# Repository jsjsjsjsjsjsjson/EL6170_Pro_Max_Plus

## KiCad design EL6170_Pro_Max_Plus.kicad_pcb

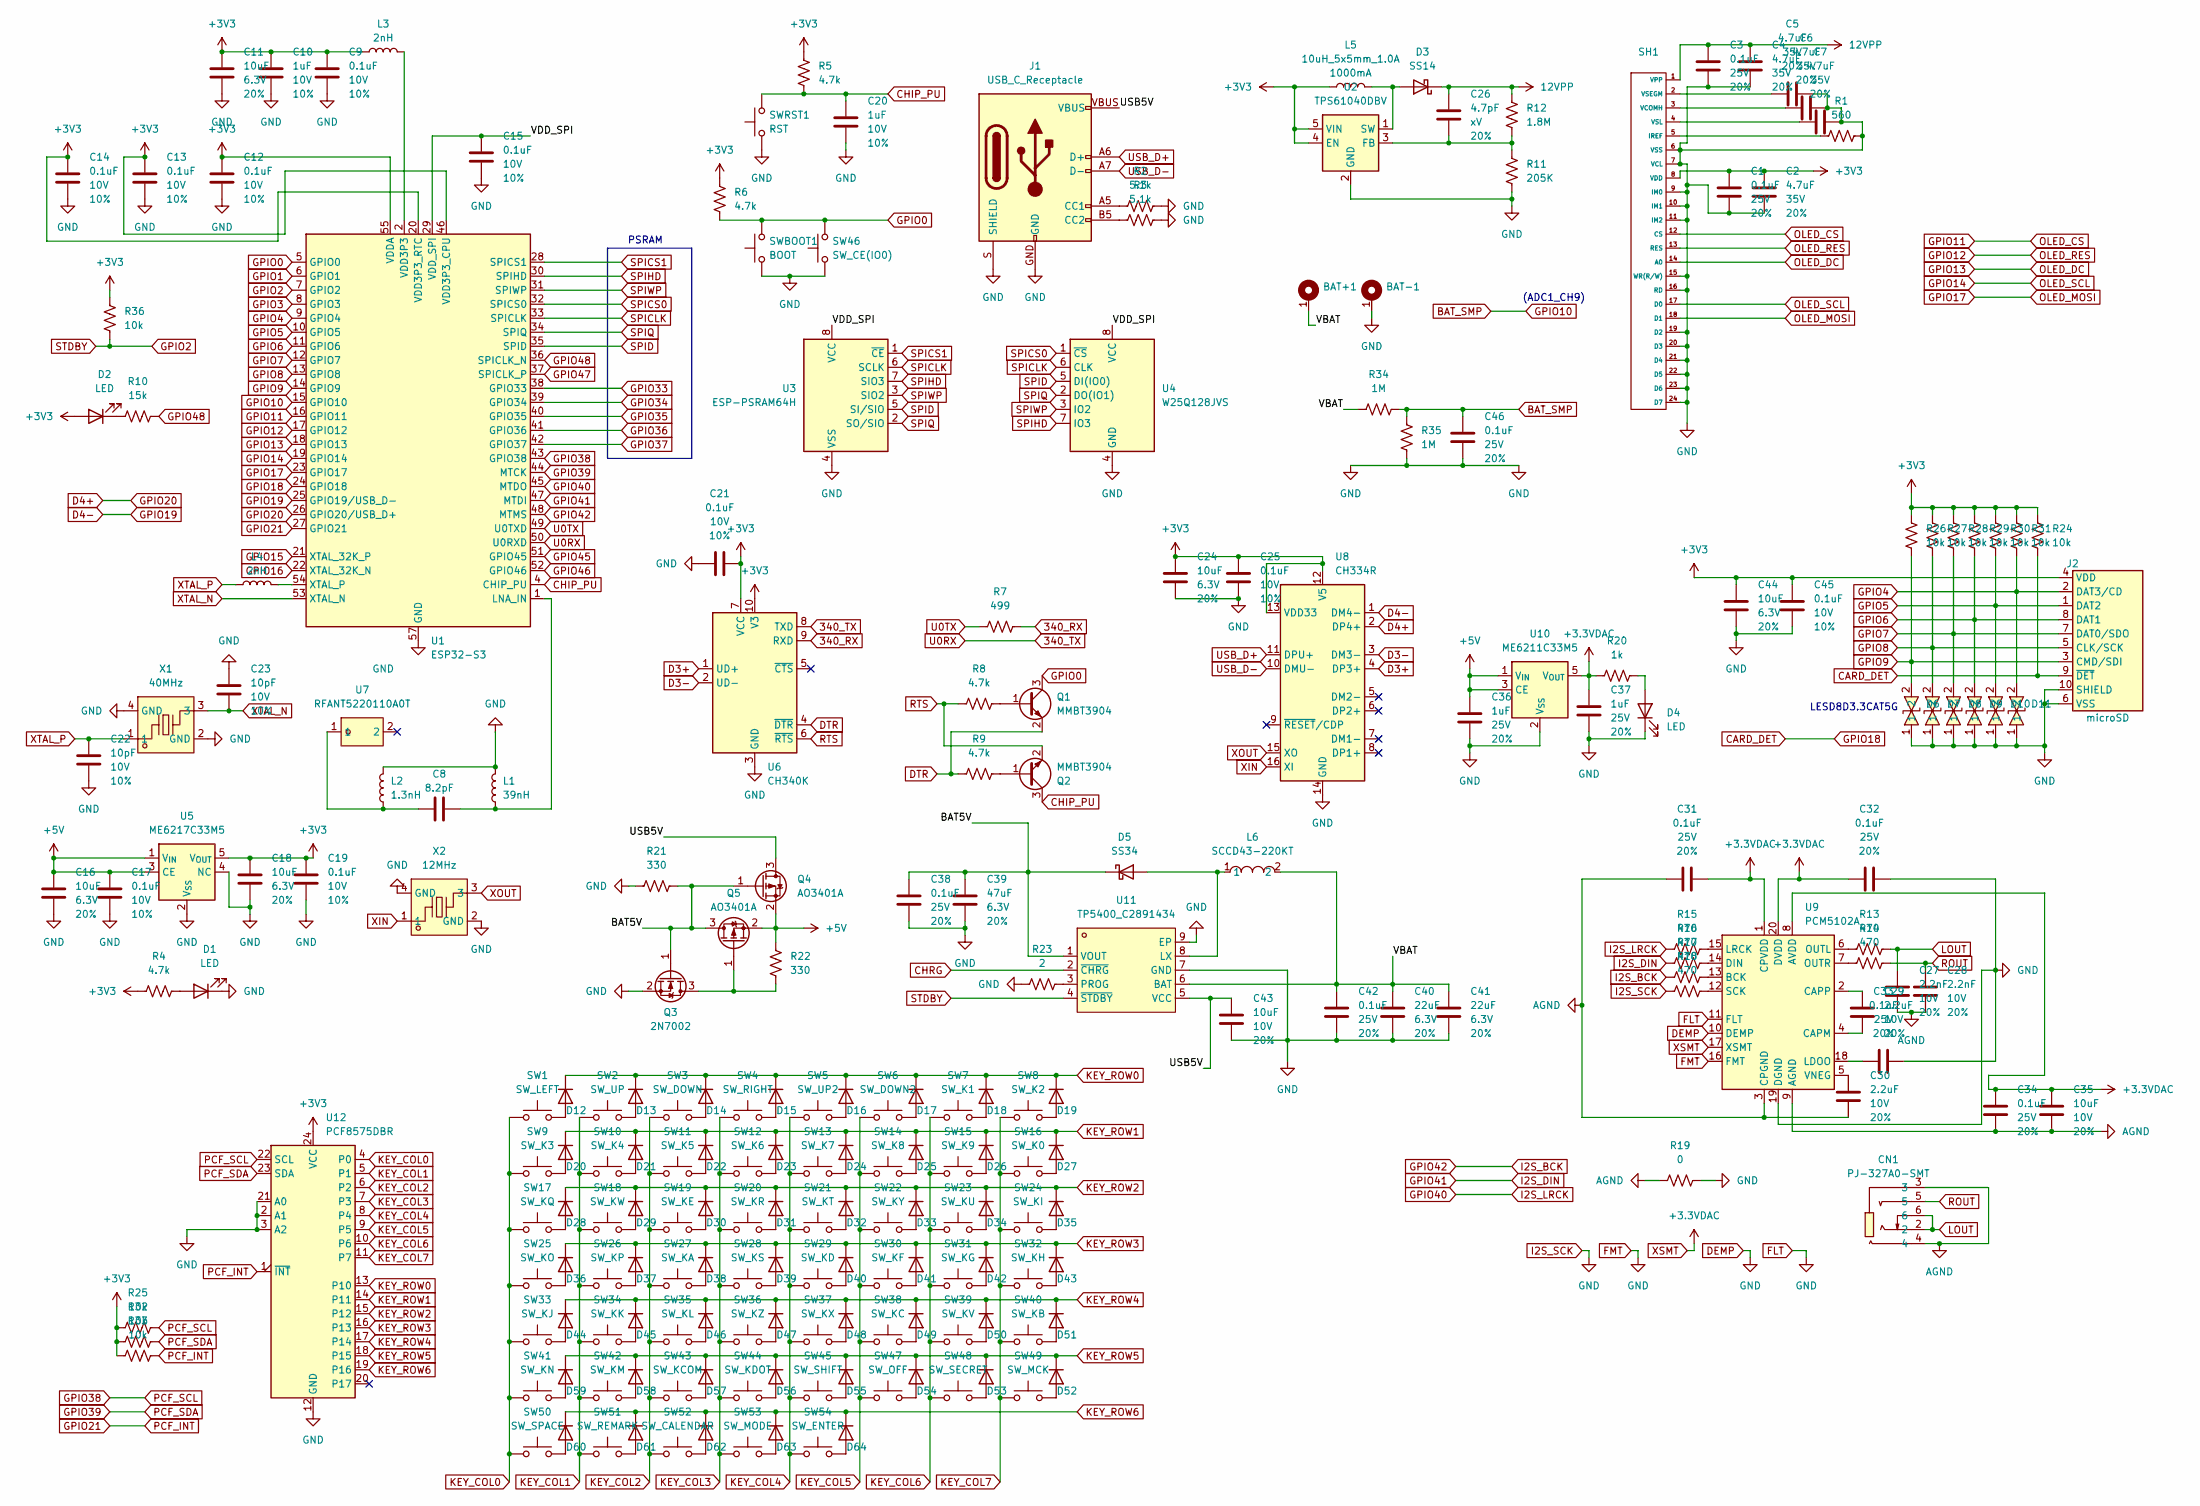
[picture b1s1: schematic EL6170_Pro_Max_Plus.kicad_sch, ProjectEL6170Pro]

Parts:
BAT+1: TestPoint_Pad_2.0x2.0mm
BAT-1: TestPoint_Pad_2.0x2.0mm
C1, C3, C31, C32, C33, C34, C38, C42, C46: 0.1uF; C_0603_1608Metric; Voltage 25V; Tolerance 20%
C2, C4, C5, C6, C7: 4.7uF; C_0603_1608Metric; Voltage 35V; Tolerance 20%
C8: 8.2pF; C_0402_1005Metric
C9, C12, C13, C14, C15, C17, C19, C21, C25, C45: 0.1uF; C_0402_1005Metric; Voltage 10V; Tolerance 10%
C10, C20: 1uF; C_0402_1005Metric; Voltage 10V; Tolerance 10%
C11, C16, C18, C24, C44: 10uF; C_0402_1005Metric; Voltage 6.3V; Tolerance 20%
C22, C23: 10pF; C_0603_1608Metric; Voltage 10V; Tolerance 10%
C26: 4.7pF; C_0402_1005Metric; Voltage xV; Tolerance 20%
C27, C28: 2.2nF; C_0603_1608Metric; Voltage 10V; Tolerance 20%
C29, C30: 2.2uF; C_0603_1608Metric; Voltage 10V; Tolerance 20%
C35, C43: 10uF; C_0603_1608Metric; Voltage 10V; Tolerance 20%
C36, C37: 1uF; C_0603_1608Metric; Voltage 25V; Tolerance 20%
C39: 47uF; C_0805_2012Metric; Voltage 6.3V; Tolerance 20%
C40, C41: 22uF; C_0603_1608Metric; Voltage 6.3V; Tolerance 20%
CN1: PJ-327A0-SMT; AUDIO-SMD_PJ-327A0-SMT; LCSC Part C381135
D1, D2, D4: LED; LED_0603_1608Metric
D3: SS14; D_SMA
D5: SS34; D_SMA
D6, D7, D8, D9, D10, D11: LESD8D3.3CAT5G; D_SOD-882; LCSC Part C172409
D12, D13, D14, D15, D16, D17, D18, D19, D20, D21, D22, D23, D24, D25, D26, D27, D28, D29, D30, D31, D32, D33, D34, D35, D36, D37, D38, D39, D40, D41, D42, D43, D44, D45, D46, D47, D48, D49, D50, D51, D52, D53, D54, D55, D56, D57, D58, D59, D60, D61, D62, D63, D64: 1N4148WS; D_SOD-323
J1: USB_C_Receptacle; USB-C_16
J2: microSD; microSD_External_Pin
L1: 39nH; L_0402_1005Metric
L2: 1.3nH; L_0402_1005Metric
L3, L4: 2nH; L_0402_1005Metric
L5: 10uH_5x5mm_1.0A; Inductor_4.7x4.7mm
L6: SCCD43-220KT; IND-SMD_L4.5-W4.0_SCCD43; LCSC Part C532863
Q1, Q2: MMBT3904; SOT-23
Q3: 2N7002; SOT-23
Q4, Q5: AO3401A; SOT-23
R1: 560; R_0402_1005Metric
R2, R3: 5.1k; R_0402_1005Metric
R4, R5, R6, R8, R9: 4.7k; R_0402_1005Metric
R7: 499; R_0402_1005Metric
R10: 15k; R_0603_1608Metric
R11: 205K; R_0603_1608Metric
R12: 1.8M; R_0603_1608Metric
R13, R14, R15, R16, R17, R18: 470; R_0603_1608Metric
R19: 0; R_0603_1608Metric
R20: 1k; R_0603_1608Metric
R21, R22: 330; R_0603_1608Metric
R23: 2; R_0603_1608Metric
R24, R25, R26, R27, R28, R29, R30, R31, R32, R33, R36: 10k; R_0402_1005Metric
R34, R35: 1M; R_0603_1608Metric
SH1: SH1122_FPC
SW1: SW_LEFT; MaskBtm6mmBh
SW2: SW_UP; MaskBtm6mm
SW3: SW_DOWN; MaskBtm6mm
SW4: SW_RIGHT; MaskBtm6mmBh
SW5: SW_UP2; MaskBtm6mm
SW6: SW_DOWN2; MaskBtm6mm
SW7: SW_K1; MaskBtm4mmBh
SW8: SW_K2; MaskBtm4mmBh
SW9: SW_K3; MaskBtm4mmBh
SW10: SW_K4; MaskBtm4mmBh
SW11: SW_K5; MaskBtm4mmBh
SW12: SW_K6; MaskBtm4mmBh
SW13: SW_K7; MaskBtm4mmBh
SW14: SW_K8; MaskBtm4mmBh
SW15: SW_K9; MaskBtm4mmBh
SW16: SW_K0; MaskBtm4mmBh
SW17: SW_KQ; MaskBtm5mm
SW18: SW_KW; MaskBtm5mm
SW19: SW_KE; MaskBtm5mm
SW20: SW_KR; MaskBtm5mm
SW21: SW_KT; MaskBtm5mm
SW22: SW_KY; MaskBtm5mm
SW23: SW_KU; MaskBtm5mm
SW24: SW_KI; MaskBtm5mm
SW25: SW_KO; MaskBtm5mm
SW26: SW_KP; MaskBtm5mm
SW27: SW_KA; MaskBtm5mm
SW28: SW_KS; MaskBtm5mm
SW29: SW_KD; MaskBtm5mm
SW30: SW_KF; MaskBtm5mm
SW31: SW_KG; MaskBtm5mm
SW32: SW_KH; MaskBtm5mm
SW33: SW_KJ; MaskBtm5mm
SW34: SW_KK; MaskBtm5mm
SW35: SW_KL; MaskBtm5mm
SW36: SW_KZ; MaskBtm5mm
SW37: SW_KX; MaskBtm5mm
SW38: SW_KC; MaskBtm5mm
SW39: SW_KV; MaskBtm5mm
SW40: SW_KB; MaskBtm5mm
SW41: SW_KN; MaskBtm5mm
SW42: SW_KM; MaskBtm5mm
SW43: SW_KCOM; MaskBtm5mm
SW44: SW_KDOT; MaskBtm5mm
SW45: SW_SHIFT; MaskBtm5mm
SW46: SW_CE(IO0); MaskBtm5mm
SW47: SW_OFF; MaskBtm5mm
SW48: SW_SECRET; MaskBtm5mm
SW49: SW_MCK; MaskBtm5mm
SW50: SW_SPACE; MaskBtm5mmBh
SW51: SW_REMARK; MaskBtm5mm
SW52: SW_CALENDAR; MaskBtm5mm
SW53: SW_MODE; MaskBtm5mm
SW54: SW_ENTER; MaskBtm5mmBh
SWBOOT1: BOOT; MaskBtm4mm
SWRST1: RST; MaskBtm4mm
U1: ESP32-S3; QFN-56-1EP_7x7mm_P0.4mm_EP4x4mm
U2: TPS61040DBV; SOT-23-5
U3: ESP-PSRAM64H; SOIC-8_3.9x4.9mm_P1.27mm
U4: W25Q128JVS; SOIC-8_5.23x5.23mm_P1.27mm
U5: ME6217C33M5; SOT-23-5
U6: CH340K; SSOP-10-1EP_3.9x4.9mm_P1mm_EP2.1x3.3mm
U7: RFANT5220110A0T; FILTER-SMD_L5.2-W2.0-L; LCSC Part C127611
U8: CH334R; QSOP-16_3.9x4.9mm_P0.635mm
U9: PCM5102A; TSSOP-20_4.4x6.5mm_P0.65mm
U10: ME6211C33M5; SOT-23-5
U11: TP5400_C2891434; ESOP-8_L4.9-W3.9-P1.27-LS6.0-BL-EP; LCSC Part C2891434
U12: PCF8575DBR; SSOP-24_5.3x8.2mm_P0.65mm
X1: 40MHz; CRYSTAL-SMD_4P-L2.5-W2.0-BL; LCSC Part C555614
X2: 12MHz; CRYSTAL-SMD_4P-L2.5-W2.0-BL-A; LCSC Part C2896601

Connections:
12VPP: C3.1, C4.1, C26.2, D3.1 (K), R12.1, SH1.1 (VPP)
340_RX: R7.1, U6.9 (RXD)
340_TX: U1.50 (U0RXD), U6.8 (TXD)
+3V3: C1.1, C2.1, C9.1, C10.1, C11.1, C12.1, C13.1, C14.1, C18.1, C19.1, C21.2, C24.1, C25.1, C44.1, C45.1, D2.2 (A), J2.4 (VDD), L3.1, L5.1, R4.2, R5.1, R6.1, R24.1, R25.1, R26.1, R27.1, R28.1, R29.1, R30.1, R31.1, R32.1, R33.1, R36.1, SH1.8 (VDD), U1.20 (VDD3P3_RTC), U1.46 (VDD3P3_CPU), U1.55 (VDDA), U1.56 (VDDA), U2.4 (EN), U2.5 (VIN), U5.5 (V_{OUT}), U6.7 (VCC), U6.10 (V3), U8.12 (V5), U8.13 (VDD33), U12.24 (VCC)
+5V: C16.1, C17.1, C36.1, Q4.2 (S), Q5.2 (S), R22.1, U5.1 (V_{IN}), U5.3 (CE), U10.1 (V_{IN}), U10.3 (CE)
/BAT5V: C38.1, C39.1, D5.1 (K), Q3.1 (G), Q4.1 (G), Q5.3 (D), R21.1, U11.1 (VOUT)
/USB5V: C43.1, J1.VBUS, Q4.3 (D), U11.5 (VCC)
/VBAT: BAT+1.1, C40.1, C41.1, C42.1, L6.2, R34.2, U11.6 (BAT)
/VDD_SPI: C15.1, U1.29 (VDD_SPI), U3.8 (VCC), U4.8 (VCC)
AGND: C27.2, C28.2, C30.2, C31.1, C34.1, C35.2, CN1.3, CN1.4, R19.2, U9.3 (CPGND), U9.9 (AGND)
BAT_SMP: C46.1, R34.1, R35.1, U1.15 (GPIO10)
CARD_DET: J2.9 (~DET), R24.2, U1.24 (GPIO18)
CHIP_PU: C20.1, Q2.3 (C), R5.2, SWRST1.2, U1.4 (CHIP_PU)
CHRG: U11.2 (~CHRG)
D3+: U6.1 (UD+), U8.4 (DP3+)
D3-: U6.2 (UD-), U8.3 (DM3-)
D4+: U1.26 (GPIO20/USB_D+), U8.2 (DP4+)
D4-: U1.25 (GPIO19/USB_D-), U8.1 (DM4-)
DEMP: BAT-1.1, C1.2, C2.2, C3.2, C4.2, C5.2, C6.2, C7.2, C9.2, C10.2, C11.2, C12.2, C13.2, C14.2, C15.2, C16.2, C17.2, C18.2, C19.2, C20.2, C21.1, C22.2, C23.1, C24.2, C25.2, C32.2, C33.2, C36.2, C37.2, C38.2, C39.2, C40.2, C41.2, C42.2, C43.2, C44.2, C45.2, C46.2, D1.1 (K), D4.1 (K), D6.1, D7.1, D8.1, D9.1, D10.1, D11.1, J1.GND, J1.S (SHIELD), J2.6 (VSS), J2.10 (SHIELD), L1.2, L2.2, Q3.2 (S), R1.1, R2.1, R3.1, R11.2, R18.2, R19.1, R21.2, R23.2, R35.2, SH1.6 (VSS), SH1.7 (VCL), SH1.9 (IM0), SH1.10 (IM1), SH1.11 (IM2), SH1.15 (WR(R/W)), SH1.16 (RD), SH1.19 (D2), SH1.20 (D3), SH1.21 (D4), SH1.22 (D5), SH1.23 (D6), SH1.24 (D7), SW46.1, SWBOOT1.1, SWRST1.1, U1.57 (GND), U2.2 (GND), U3.4 (VSS), U4.4 (GND), U5.2 (V_{SS}), U5.4 (NC), U6.3 (GND), U6.11 (GND), U8.14 (GND), U9.10 (DEMP), U9.11 (FLT), U9.16 (FMT), U9.19 (DGND), U10.2 (V_{SS}), U11.7 (GND), U11.9 (EP), U12.2 (A1), U12.3 (A2), U12.12 (GND), U12.21 (A0), X1.2 (GND), X1.4 (GND), X2.2 (GND), X2.4 (GND)
DTR: Q1.2 (E), R9.1, U6.4 (~DTR)
GPIO0: Q1.3 (C), R6.2, SW46.2, SWBOOT1.2, U1.5 (GPIO0)
GPIO1: U1.6 (GPIO1)
GPIO2: R36.2, U1.7 (GPIO2), U11.4 (~STDBY)
GPIO3: U1.8 (GPIO3)
GPIO4: D11.2, J2.2 (DAT3/CD), R31.2, U1.9 (GPIO4)
GPIO5: D10.2, J2.1 (DAT2), R30.2, U1.10 (GPIO5)
GPIO6: D9.2, J2.8 (DAT1), R29.2, U1.11 (GPIO6)
GPIO7: D8.2, J2.7 (DAT0/SDO), R28.2, U1.12 (GPIO7)
GPIO8: D7.2, J2.5 (CLK/SCK), R27.2, U1.13 (GPIO8)
GPIO9: D6.2, J2.3 (CMD/SDI), R26.2, U1.14 (GPIO9)
GPIO11: SH1.12 (CS), U1.16 (GPIO11)
GPIO12: SH1.13 (RES), U1.17 (GPIO12)
GPIO13: SH1.14 (A0), U1.18 (GPIO13)
GPIO14: SH1.17 (D0), U1.19 (GPIO14)
GPIO15: U1.21 (XTAL_32K_P)
GPIO16: U1.22 (XTAL_32K_N)
GPIO17: SH1.18 (D1), U1.23 (GPIO17)
GPIO21: R33.2, U1.27 (GPIO21), U12.1 (~INT)
GPIO33: U1.38 (GPIO33)
GPIO34: U1.39 (GPIO34)
GPIO35: U1.40 (GPIO35)
GPIO36: U1.41 (GPIO36)
GPIO37: U1.42 (GPIO37)
GPIO38: R25.2, U1.43 (GPIO38), U12.22 (SCL)
GPIO39: R32.2, U1.44 (MTCK), U12.23 (SDA)
GPIO40: R15.2, U1.45 (MTDO)
GPIO41: R16.2, U1.47 (MTDI)
GPIO42: R17.2, U1.48 (MTMS)
GPIO45: U1.51 (GPIO45)
GPIO46: U1.52 (GPIO46)
GPIO47: U1.37 (SPICLK_P)
GPIO48: R10.1, U1.36 (SPICLK_N)
KEY_COL0: SW1.1, SW9.1, SW17.1, SW25.1, SW33.1, SW41.1, SW50.1, U12.4 (P0)
KEY_COL1: SW2.1, SW10.1, SW18.1, SW26.1, SW34.1, SW42.1, SW51.1, U12.5 (P1)
KEY_COL2: SW3.1, SW11.1, SW19.1, SW27.1, SW35.1, SW43.1, SW52.1, U12.6 (P2)
KEY_COL3: SW4.1, SW12.1, SW20.1, SW28.1, SW36.1, SW44.1, SW53.1, U12.7 (P3)
KEY_COL4: SW5.1, SW13.1, SW21.1, SW29.1, SW37.1, SW45.1, SW54.1, U12.8 (P4)
KEY_COL5: SW6.1, SW14.1, SW22.1, SW30.1, SW38.1, SW47.1, U12.9 (P5)
KEY_COL6: SW7.1, SW15.1, SW23.1, SW31.1, SW39.1, SW48.1, U12.10 (P6)
KEY_COL7: SW8.1, SW16.1, SW24.1, SW32.1, SW40.1, SW49.1, U12.11 (P7)
KEY_ROW0: D12.1 (K), D13.1 (K), D14.1 (K), D15.1 (K), D16.1 (K), D17.1 (K), D18.1 (K), D19.1 (K), U12.13 (P10)
KEY_ROW1: D20.1 (K), D21.1 (K), D22.1 (K), D23.1 (K), D24.1 (K), D25.1 (K), D26.1 (K), D27.1 (K), U12.14 (P11)
KEY_ROW2: D28.1 (K), D29.1 (K), D30.1 (K), D31.1 (K), D32.1 (K), D33.1 (K), D34.1 (K), D35.1 (K), U12.15 (P12)
KEY_ROW3: D36.1 (K), D37.1 (K), D38.1 (K), D39.1 (K), D40.1 (K), D41.1 (K), D42.1 (K), D43.1 (K), U12.16 (P13)
KEY_ROW4: D44.1 (K), D45.1 (K), D46.1 (K), D47.1 (K), D48.1 (K), D49.1 (K), D50.1 (K), D51.1 (K), U12.17 (P14)
KEY_ROW5: D52.1 (K), D53.1 (K), D54.1 (K), D55.1 (K), D56.1 (K), D57.1 (K), D58.1 (K), D59.1 (K), U12.18 (P15)
KEY_ROW6: D60.1 (K), D61.1 (K), D62.1 (K), D63.1 (K), D64.1 (K), U12.19 (P16)
LOUT: C27.1, CN1.2, CN1.6, R13.1
unnamed: C8.2, L2.1, U7.1
unnamed: D1.2 (A), R4.1
unnamed: D2.1 (K), R10.2
unnamed: D3.2 (A), L5.2, U2.1 (SW)
unnamed: D4.2 (A), R20.1
unnamed: D5.2 (A), L6.1, U11.8 (LX)
unnamed: D12.2 (A), SW1.2
unnamed: D13.2 (A), SW2.2
unnamed: D14.2 (A), SW3.2
unnamed: D15.2 (A), SW4.2
unnamed: D16.2 (A), SW5.2
unnamed: D17.2 (A), SW6.2
unnamed: D18.2 (A), SW7.2
unnamed: D19.2 (A), SW8.2
unnamed: D20.2 (A), SW9.2
unnamed: D21.2 (A), SW10.2
unnamed: D22.2 (A), SW11.2
unnamed: D23.2 (A), SW12.2
unnamed: D24.2 (A), SW13.2
unnamed: D25.2 (A), SW14.2
unnamed: D26.2 (A), SW15.2
unnamed: D27.2 (A), SW16.2
unnamed: D28.2 (A), SW17.2
unnamed: D29.2 (A), SW18.2
unnamed: D30.2 (A), SW19.2
unnamed: D31.2 (A), SW20.2
unnamed: D32.2 (A), SW21.2
unnamed: D33.2 (A), SW22.2
unnamed: D34.2 (A), SW23.2
unnamed: D35.2 (A), SW24.2
unnamed: D36.2 (A), SW25.2
unnamed: D37.2 (A), SW26.2
unnamed: D38.2 (A), SW27.2
unnamed: D39.2 (A), SW28.2
unnamed: D40.2 (A), SW29.2
unnamed: D41.2 (A), SW30.2
unnamed: D42.2 (A), SW31.2
unnamed: D43.2 (A), SW32.2
unnamed: D44.2 (A), SW33.2
unnamed: D45.2 (A), SW34.2
unnamed: D46.2 (A), SW35.2
unnamed: D47.2 (A), SW36.2
unnamed: D48.2 (A), SW37.2
unnamed: D49.2 (A), SW38.2
unnamed: D50.2 (A), SW39.2
unnamed: D51.2 (A), SW40.2
unnamed: D52.2 (A), SW49.2
unnamed: D53.2 (A), SW48.2
unnamed: D54.2 (A), SW47.2
unnamed: D55.2 (A), SW45.2
unnamed: D56.2 (A), SW44.2
unnamed: D57.2 (A), SW43.2
unnamed: D58.2 (A), SW42.2
unnamed: D59.2 (A), SW41.2
unnamed: D60.2 (A), SW50.2
unnamed: D61.2 (A), SW51.2
unnamed: D62.2 (A), SW52.2
unnamed: D63.2 (A), SW53.2
unnamed: D64.2 (A), SW54.2
unnamed: J1.A5 (CC1), R2.2
unnamed: J1.B5 (CC2), R3.2
unnamed: L3.2, U1.2 (VDD3P3), U1.3 (VDD3P3)
unnamed: Q1.1 (B), R8.2
unnamed: Q2.1 (B), R9.2
unnamed: Q3.3 (D), Q5.1 (G), R22.2
unnamed: R1.2, SH1.5 (IREF)
unnamed: C6.1, SH1.3 (VCOMH)
unnamed: C5.1, SH1.2 (VSEGM)
unnamed: C7.1, SH1.4 (VSL)
unnamed: C8.1, L1.1, U1.1 (LNA_IN)
unnamed: L4.2, U1.54 (XTAL_P)
unnamed: C26.1, R11.1, R12.2, U2.3 (FB)
unnamed: R17.1, U9.13 (BCK)
unnamed: C29.2, U9.4 (CAPM)
unnamed: C29.1, U9.2 (CAPP)
unnamed: R16.1, U9.14 (DIN)
unnamed: C33.1, U9.18 (LDOO)
unnamed: R15.1, U9.15 (LRCK)
unnamed: R13.2, U9.6 (OUTL)
unnamed: R14.2, U9.7 (OUTR)
unnamed: R18.1, U9.12 (SCK)
unnamed: C30.1, U9.5 (VNEG)
unnamed: R23.1, U11.3 (PROG)
ROUT: C28.1, CN1.5, R14.1
RTS: Q2.2 (E), R8.1, U6.6 (~RTS)
SPICLK: U1.33 (SPICLK), U3.6 (SCLK), U4.6 (CLK)
SPICS0: U1.32 (SPICS0), U4.1 (~CS)
SPICS1: U1.28 (SPICS1), U3.1 (~CE)
SPID: U1.35 (SPID), U3.5 (SI/SIO), U4.5 (DI(IO0))
SPIHD: U1.30 (SPIHD), U3.7 (SIO3), U4.7 (IO3)
SPIQ: U1.34 (SPIQ), U3.2 (SO/SIO), U4.2 (DO(IO1))
SPIWP: U1.31 (SPIWP), U3.3 (SIO2), U4.3 (IO2)
U0TX: R7.2, U1.49 (U0TXD)
USB_D+: J1.A6 (D+), J1.B6 (D+), U8.11 (DPU+)
USB_D-: J1.A7 (D-), J1.B7 (D-), U8.10 (DMU-)
XIN: U8.16 (XI), X2.1
XOUT: U8.15 (XO), X2.3
XSMT: C31.2, C32.1, C34.2, C35.1, C37.1, R20.2, U9.1 (CPVDD), U9.8 (AVDD), U9.17 (XSMT), U9.20 (DVDD), U10.5 (V_{OUT})
XTAL_N: C23.2, U1.53 (XTAL_N), X1.3
XTAL_P: C22.1, L4.1, X1.1

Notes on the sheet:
LESD8D3.3CAT5G
(ADC1_CH9)
PSRAM

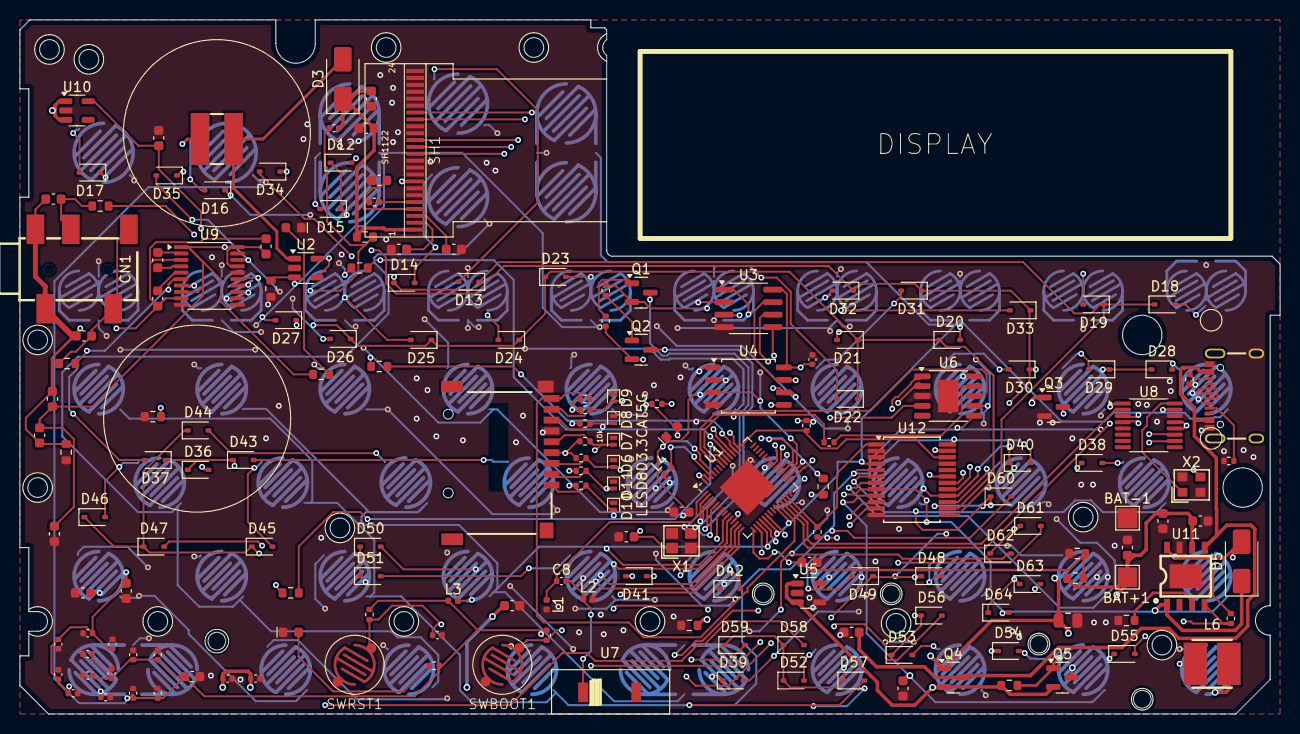
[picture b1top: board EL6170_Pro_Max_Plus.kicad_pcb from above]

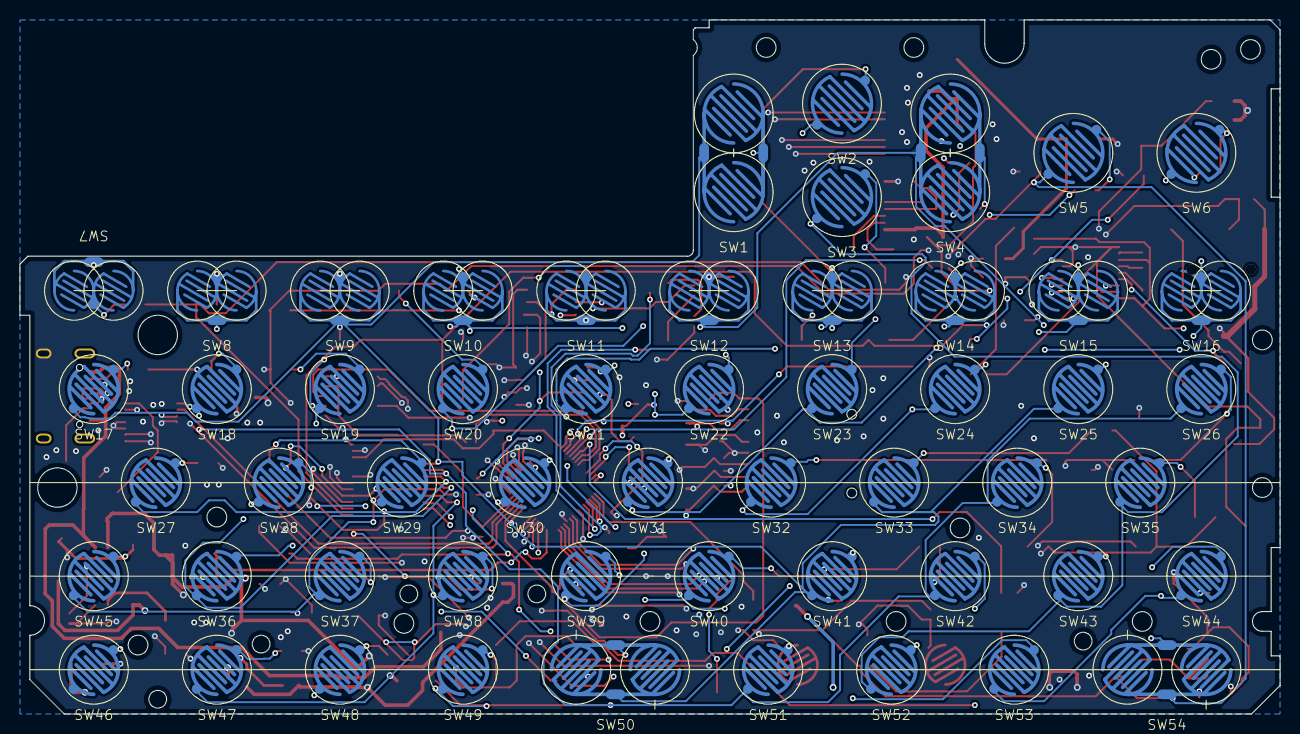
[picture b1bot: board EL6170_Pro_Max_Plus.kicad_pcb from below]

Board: 4 copper layers, 128.0 x 70.5 mm, 233 parts (54 on the bottom side), 155 nets.

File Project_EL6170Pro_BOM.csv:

"Reference","Value","Datasheet","Footprint","Qty","DNP"
"Audio1","PJ-320B","https://lcsc.com/product-detail/Audio-Connectors_3-5mmCloth-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","easyeda2kicad:AUDIO-SMD_PJ-320B","1",""
"BAT+1,BAT-1,SH1","~","","-- 混合值 --","3",""
"C1,C3,C17,C19,C21,C25,C31,C32,C33,C34,C38,C42,C45,C46,C49","0.1uF","https://cdn.sparkfun.com/assets/8/a/4/a/5/Kemet_Capacitor_Da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","-- 混合值 --","15",""
"C2,C4,C5,C6,C7","4.7uF","https://cdn.sparkfun.com/assets/8/a/4/a/5/Kemet_Capacitor_Da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","SparkFun-Capacitor:C_0603_1608Metric","5",""
"C16,C18,C24,C35,C43,C44","10uF","https://cdn.sparkfun.com/assets/8/a/4/a/5/Kemet_Capacitor_Da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","-- 混合值 --","6",""
"C20,C36,C37","1uF","https://cdn.sparkfun.com/assets/8/a/4/a/5/Kemet_Capacitor_Da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","-- 混合值 --","3",""
"C26","4.7pF","https://cdn.sparkfun.com/assets/8/a/4/a/5/Kemet_Capacitor_Da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","SparkFun-Capacitor:C_0402_1005Metric","1",""
"C27,C28","2.2nF","https://cdn.sparkfun.com/assets/8/a/4/a/5/Kemet_Capacitor_Da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","SparkFun-Capacitor:C_0603_1608Metric","2",""
"C29,C30","2.2uF","https://cdn.sparkfun.com/assets/8/a/4/a/5/Kemet_Capacitor_Da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","SparkFun-Capacitor:C_0603_1608Metric","2",""
"C39","47uF","https://cdn.sparkfun.com/assets/8/a/4/a/5/Kemet_Capacitor_Da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","SparkFun-Capacitor:C_0805_2012Metric","1",""
"C40,C41,C50","22uF","https://cdn.sparkfun.com/assets/8/a/4/a/5/Kemet_Capacitor_Da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","SparkFun-Capacitor:C_0603_1608Metric","3",""
"C47,C48","12pF","https://cdn.sparkfun.com/assets/8/a/4/a/5/Kemet_Capacitor_Da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","SparkFun-Capacitor:C_0402_1005Metric","2",""
"D2","LED","~","SparkFun-LED:LED_0603_1608Metric","1",""
"D3","SS14","https://www.vishay.com/docs/88746/ss12.pdf","Diode_SMD:D_SMA","1",""
"D5","SS34","https://www.vishay.com/docs/88751/ss32.pdf","Diode_SMD:D_SMA","1",""
"D6,D7,D8,D9,D10,D11","LESD8D3.3CAT5G","","Diode_SMD:D_SOD-882","6",""
"J2","microSD","https://datasheet.lcsc.com/lcsc/2110151630_XKB-Connectivity-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","SparkFun-Connector:microSD_External_Pin","1",""
"L5","10uH_5x5mm_1.0A","https://products.sumida.com/products/pdf/CDRH4D28.pdf","SparkFun-Coil:Inductor_4.7x4.7mm","1",""
"L6","SCCD43-220KT","","easyeda2kicad:IND-SMD_L4.5-W4.0_SCCD43","1",""
"Q1,Q2","MMBT3904","https://www.onsemi.com/pdf/datasheet/pzt3904-d.pdf","Package_TO_SOT_SMD:SOT-23","2",""
"Q3","2N7002","https://www.onsemi.com/pub/Collateral/NDS7002A-D.PDF","Package_TO_SOT_SMD:SOT-23","1",""
"Q4,Q5","AO3401A","http://www.aosmd.com/pdfs/datasheet/AO3401A.pdf","Package_TO_SOT_SMD:SOT-23","2",""
"R1","560","https://www.vishay.com/docs/20035/dcrcwe3.pdf","SparkFun-Resistor:R_0402_1005Metric","1",""
"R4,R19","0","https://industrial.panasonic.com/cdbs/www-data/pdf/RDN0000/A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","-- 混合值 --","2",""
"R5,R6,R8,R9","4.7k","https://www.vishay.com/docs/20035/dcrcwe3.pdf","SparkFun-Resistor:R_0402_1005Metric","4",""
"R7","499","https://industrial.panasonic.com/cdbs/www-data/pdf/RDN0000/A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","SparkFun-Resistor:R_0402_1005Metric","1",""
"R10","15k","https://www.vishay.com/docs/20035/dcrcwe3.pdf","SparkFun-Resistor:R_0603_1608Metric","1",""
"R11","205K","https://industrial.panasonic.com/cdbs/www-data/pdf/RDN0000/A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","SparkFun-Resistor:R_0603_1608Metric","1",""
"R12","1.8M","https://industrial.panasonic.com/cdbs/www-data/pdf/RDN0000/A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","SparkFun-Resistor:R_0603_1608Metric","1",""
"R13,R14,R15,R16,R17,R18","470","https://www.vishay.com/docs/20035/dcrcwe3.pdf","SparkFun-Resistor:R_0603_1608Metric","6",""
"R21,R22","330","https://www.vishay.com/docs/20035/dcrcwe3.pdf","SparkFun-Resistor:R_0603_1608Metric","2",""
"R23","2","https://www.vishay.com/docs/20035/dcrcwe3.pdf","SparkFun-Resistor:R_0603_1608Metric","1",""
"R24,R25,R26,R27,R28,R29,R30,R31,R32,R33,R36","10k","https://www.vishay.com/docs/20035/dcrcwe3.pdf","SparkFun-Resistor:R_0402_1005Metric","11",""
"R34,R35","1M","https://www.vishay.com/docs/20035/dcrcwe3.pdf","SparkFun-Resistor:R_0603_1608Metric","2",""
"SW1","SW_LEFT","~","Butm:MaskBtm6mmBh","1",""
"SW2","SW_UP","~","Butm:MaskBtm6mm","1",""
"SW3","SW_DOWN","~","Butm:MaskBtm6mm","1",""
"SW4","SW_RIGHT","~","Butm:MaskBtm6mmBh","1",""
"SW5","SW_UP2","~","Butm:MaskBtm6mm","1",""
"SW6","SW_DOWN2","~","Butm:MaskBtm6mm","1",""
"SW7","SW_K1","~","Butm:MaskBtm4mmBh","1",""
"SW8","SW_K2","~","Butm:MaskBtm4mmBh","1",""
"SW9","SW_K3","~","Butm:MaskBtm4mmBh","1",""
"SW10","SW_K4","~","Butm:MaskBtm4mmBh","1",""
"SW11","SW_K5","~","Butm:MaskBtm4mmBh","1",""
"SW12","SW_K6","~","Butm:MaskBtm4mmBh","1",""
"SW13","SW_K7","~","Butm:MaskBtm4mmBh","1",""
"SW14","SW_K8","~","Butm:MaskBtm4mmBh","1",""
"SW15","SW_K9","~","Butm:MaskBtm4mmBh","1",""
"SW16","SW_K0","~","Butm:MaskBtm4mmBh","1",""
"SW17","SW_KQ","~","Butm:MaskBtm5mm","1",""
"SW18","SW_KW","~","Butm:MaskBtm5mm","1",""
"SW19","SW_KE","~","Butm:MaskBtm5mm","1",""
"SW20","SW_KR","~","Butm:MaskBtm5mm","1",""
"SW21","SW_KT","~","Butm:MaskBtm5mm","1",""
"SW22","SW_KY","~","Butm:MaskBtm5mm","1",""
"SW23","SW_KU","~","Butm:MaskBtm5mm","1",""
"SW24","SW_KI","~","Butm:MaskBtm5mm","1",""
"SW25","SW_KO","~","Butm:MaskBtm5mm","1",""
"SW26","SW_KP","~","Butm:MaskBtm5mm","1",""
"SW27","SW_KA","~","Butm:MaskBtm5mm","1",""
"SW28","SW_KS","~","Butm:MaskBtm5mm","1",""
"SW29","SW_KD","~","Butm:MaskBtm5mm","1",""
"SW30","SW_KF","~","Butm:MaskBtm5mm","1",""
"SW31","SW_KG","~","Butm:MaskBtm5mm","1",""
"SW32","SW_KH","~","Butm:MaskBtm5mm","1",""
"SW33","SW_KJ","~","Butm:MaskBtm5mm","1",""
"SW34","SW_KK","~","Butm:MaskBtm5mm","1",""
"SW35","SW_KL","~","Butm:MaskBtm5mm","1",""
"SW36","SW_KZ","~","Butm:MaskBtm5mm","1",""
"SW37","SW_KX","~","Butm:MaskBtm5mm","1",""
"SW38","SW_KC","~","Butm:MaskBtm5mm","1",""
"SW39","SW_KV","~","Butm:MaskBtm5mm","1",""
"SW40","SW_KB","~","Butm:MaskBtm5mm","1",""
"SW41","SW_KN","~","Butm:MaskBtm5mm","1",""
"SW42","SW_KM","~","Butm:MaskBtm5mm","1",""
"SW43","SW_KCOM","~","Butm:MaskBtm5mm","1",""
"SW44","SW_KDOT","~","Butm:MaskBtm5mm","1",""
"SW45","SW_SHIFT","~","Butm:MaskBtm5mm","1",""
"SW46","SW_CE(IO0)","~","Butm:MaskBtm5mm","1",""
"SW47","SW_OFF","~","Butm:MaskBtm5mm","1",""
"SW48","SW_SECRET","~","Butm:MaskBtm5mm","1",""
"SW49","SW_MCK","~","Butm:MaskBtm5mm","1",""
"SW50","SW_SPACE","~","Butm:MaskBtm5mmBh","1",""
"SW51","SW_REMARK","~","Butm:MaskBtm5mm","1",""
"SW52","SW_CALENDAR","~","Butm:MaskBtm5mm","1",""
"SW53","SW_MODE","~","Butm:MaskBtm5mm","1",""
"SW54","SW_ENTER","~","Butm:MaskBtm5mmBh","1",""
"SWBOOT1","BOOT","~","Butm:MaskBtm4mm","1",""
"SWRST1","RST","~","Butm:MaskBtm4mm","1",""
"U2","TPS61040DBV","http://www.ti.com/lit/ds/symlink/tps61040.pdf","Package_TO_SOT_SMD:SOT-23-5","1",""
"U5","ME6217C33M5","https://www.lcsc.com/datasheet/lcsc_datasheet_2304140030_MIC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","Package_TO_SOT_SMD:SOT-23-5","1",""
"U6","CH340K","https://cdn.sparkfun.com/assets/5/0/a/8/5/CH340DS1.PDF","Package_SO:SSOP-10-1EP_3.9x4.9mm_P1mm_EP2.1x3.3mm","1",""
"U8","CH334R","https://www.wch-ic.com/downloads/file/327.html","Package_SO:QSOP-16_3.9x4.9mm_P0.635mm","1",""
"U9","PCM5102A","https://www.ti.com/lit/ds/symlink/pcm5102a.pdf","Package_SO:TSSOP-20_4.4x6.5mm_P0.65mm","1",""
"U10","ME6211C33M5","https://www.lcsc.com/datasheet/lcsc_datasheet_2304140030_MIC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","Package_TO_SOT_SMD:SOT-23-5","1",""
"U11","TP5400_C2891434","","easyeda2kicad:ESOP-8_L4.9-W3.9-P1.27-LS6.0-BL-EP","1",""
"U12","PCF8575DBR","https://www.ti.com/lit/ds/symlink/pcf8575.pdf","Package_SO:SSOP-24_5.3x8.2mm_P0.65mm","1",""
"U13","ESP32-S3-WROOM-1U","https://www.espressif.com/sites/default/files/documentation/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","RF_Module:ESP32-S3-WROOM-1U","1",""
"USB1","MicroUSB","","easyeda2kicad:MICRO-USB-SMD_MICRO-XNJ-ZB","1",""
"X2","12MHz","","easyeda2kicad:CRYSTAL-SMD_4P-L2.5-W2.0-BL-A","1",""
"Y1","32.768kHz","https://abracon.com/Resonators/ABS07.pdf","SparkFun-Clock:Crystal_SMD_3.2x1.5mm","1",""

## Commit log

2024-09-18 sync
2024-09-18 add TPS61040DBV
2024-09-18 add PCM5102A
2024-09-19 add LDO
2024-09-19 add IP5306
2024-09-21 power mang
2024-09-23 add SDCARD
2024-09-25 原理图搞定啦啊哈哈哈！！！
2024-09-27 add some keypad
2024-09-27 PCB layout
2024-10-02 gerber
2024-10-02 remove DISPLAY
2024-10-02 JLCJLCJLCJLC
2024-10-02 qwerty
2024-10-03 -R E W I R E-
2024-10-03 iret
2024-10-04 REEEEEEE
2024-10-04 Remove the diode from the keyboard
2024-10-04 Remove some LED
2024-10-04 PCM5102A
2024-10-09 windows sync
2024-10-11 snap
2024-10-11 remove a zip
2024-10-11 add pdf
2024-10-12 no JLC
2024-10-15 Project EL6170Pro V3
2024-10-16 fix some paste
2024-10-16 V3_FIX
2024-10-20 V4_FIX
2024-10-20 remove backup
2024-10-21 V4 qwq
